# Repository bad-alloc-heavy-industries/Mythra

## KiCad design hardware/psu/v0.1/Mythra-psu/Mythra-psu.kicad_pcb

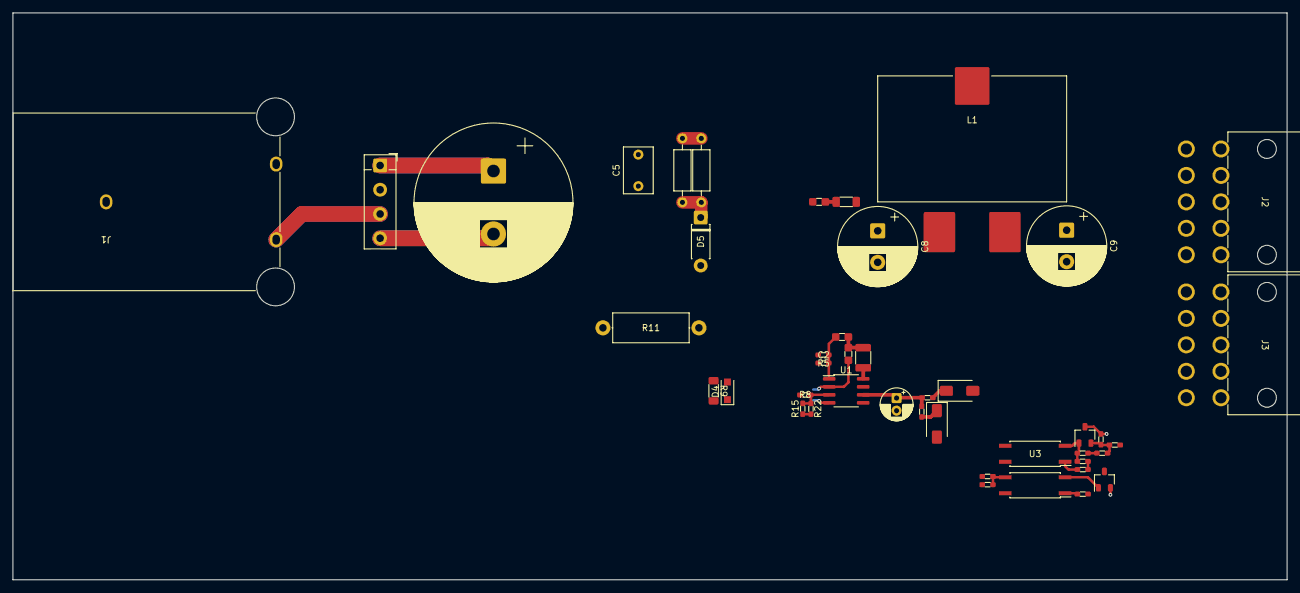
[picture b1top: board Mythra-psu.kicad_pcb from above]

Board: 4 copper layers, 202.3 x 90.0 mm, 45 parts (1 on the bottom side), 30 nets.

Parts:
C1: 470uF @ 450V; CP_Radial_D25.0mm_P10.00mm_SnapIn
C2: 100n; C0603
C3: 22u; CP_Radial_D5.0mm_P2.00mm
C5: 10n; C_Rect_L7.2mm_W4.5mm_P5.00mm_FKS2_FKP2_MKS2_MKP2
C6: 10n; C0603
C7: 1n; C1206
C8, C9: 1m; CP_Radial_D12.5mm_P5.00mm
C10: 1n; C0603
D1: KBP406GTB; Diode_Bridge_Vishay_KBPM
D2: US1M-E3/5AT; D_SMA
D3: 1SMA4744; D_SMA
D4: RB162MM-40; D_SOD-123F
D5: UF4007; D_DO-41_SOD81_P7.62mm_Horizontal
D6: MMBZ5253BLT1G; SOT-23
J1: IEC 320-C14; Schuter-5120.5073.0
J2: Output A; 39-30-1101
J3: Output B; 39-30-1101
L1: 10u; SER2915H
R1, R4: 10M; R0805
R2: 56k; R0603
R3: 0R; R0603
R5: 180k; R0603
R6, R8: 1k; R0603
R7: 50k; R1210
R9: 150R; R1206
R10, R21: 113k; R_Axial_DIN0207_L6.3mm_D2.5mm_P10.16mm_Horizontal
R11: 0R5; R_Axial_DIN0414_L11.9mm_D4.5mm_P15.24mm_Horizontal
R12, R13: 10k; R0603
R14: 10R; R0805
R15, R22: 12k; R0603
R16: 1k5; R0603
R17: 1k2; R0603
R18: 20k; R0603
R19: 60k4; R0603
R20: 6k98; R0603
U1: FAN7602C; SO-8_3.9x4.9mm_P1.27mm
U2, U3: VO617A-8X017T; SO-4_7.6x3.6mm_P2.54mm
U4: AS431BNTR-G1; SOT-23

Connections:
0V: J2.1, J2.2, J2.3, J2.4, J2.5, J3.1, J3.2, J3.3, J3.4, J3.5
+12V: J2.10, J3.10
+24V: J2.6, J2.7, J2.8, J2.9, J3.6, J3.7, J3.8, J3.9
/24V supply/24V: C9.1, L1.2, R13.1, R19.1
/24V supply/FB: R8.2, R15.2, R22.2, U1.3 (CS/FB)
/24V supply/GND: C8.2, C9.2, D6.2 (A), R20.2, U4.3 (A)
/24V supply/LUVP: C2.1, R4.2, R5.1, U1.1 (LUVP)
/24V supply/OUT: D4.1 (K), R9.2, U1.5 (OUT)
/24V supply/PLIM: R1.2, R2.1, R12.1, U1.2 (LAT/PLIM)
/24V supply/VCC: C3.1, R3.1, R6.1, U1.6 (VCC), U2.4, U3.4
/24V supply/VSTR: R7.2, U1.8 (VSTR)
/PRIM+: C1.1, C5.2, D1.1 (+), R1.1, R4.1, R7.1, R10.1, R21.1
/PRIM-: C1.2, C2.2, C3.2, C6.2, D1.4 (-), D3.2 (A), R2.2, R5.2, R11.2, U1.4 (GND)
LINE: D1.2, J1.L
NEUT: D1.3, J1.N
unnamed: C5.1, D5.1 (K), R10.2, R21.2
unnamed: C6.1, R12.2, U2.3
unnamed: C7.1, C8.1, L1.1, R16.1, R17.1
unnamed: C7.2, R14.1
unnamed: C10.1, R19.2, R20.1, U4.2 (REF)
unnamed: C10.2, R18.1
unnamed: D2.1 (K), R3.2
unnamed: D3.1 (K), R6.2
unnamed: D4.2 (A), R9.1
unnamed: D6.1 (K), U2.2
unnamed: R8.1, R11.1
unnamed: R13.2, U2.1
unnamed: R15.1, R22.1, U3.3
unnamed: R16.2, U3.1
unnamed: R17.2, R18.2, U3.2, U4.1 (K)

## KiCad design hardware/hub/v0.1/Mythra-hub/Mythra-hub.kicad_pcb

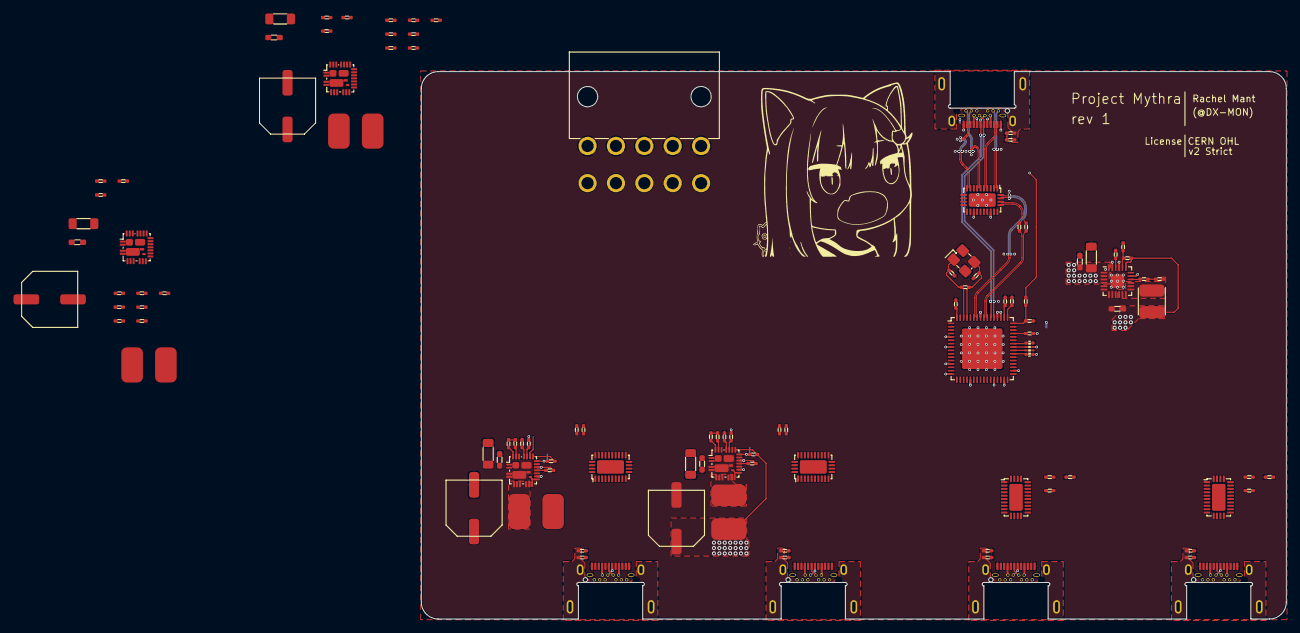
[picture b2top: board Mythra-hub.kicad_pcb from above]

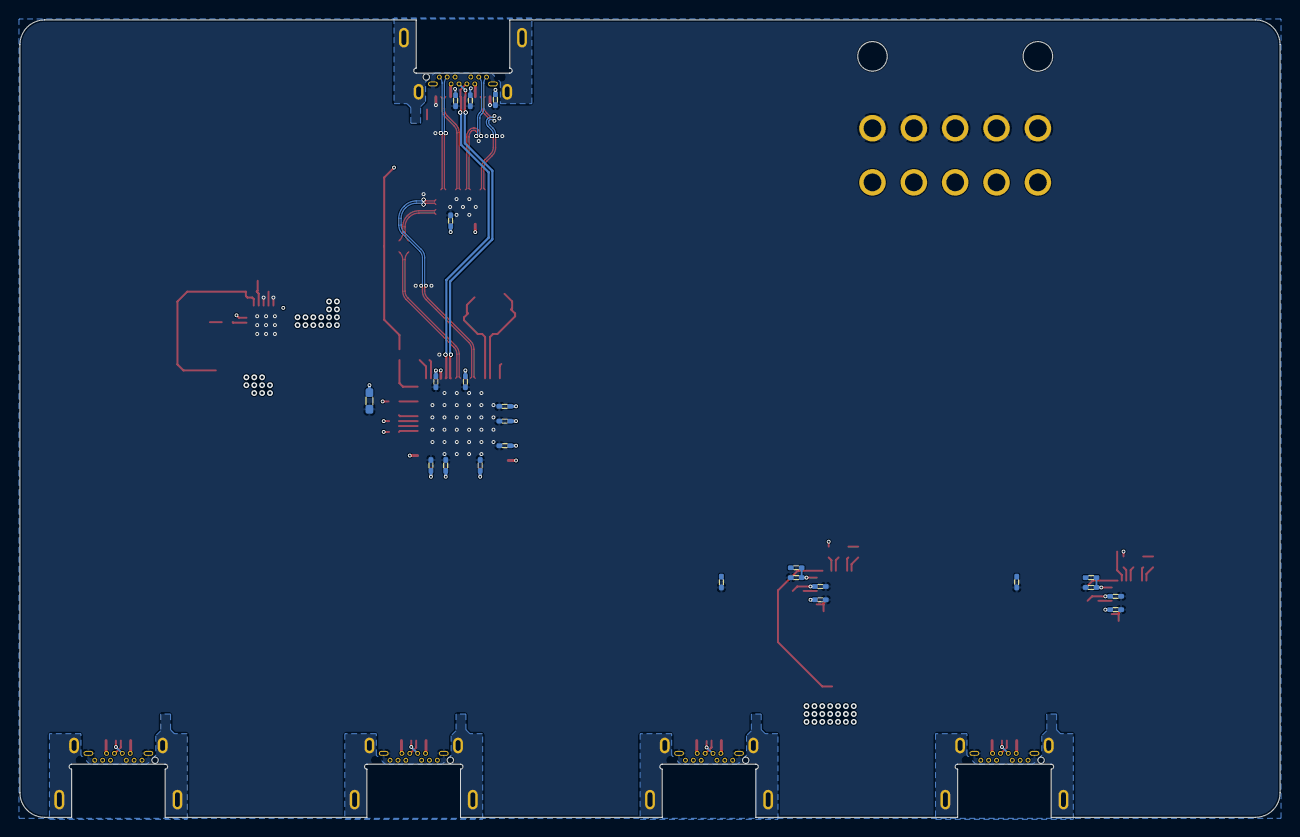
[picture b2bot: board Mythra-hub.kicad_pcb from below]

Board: 6 copper layers, 128.0 x 81.0 mm, 130 parts (23 on the bottom side), 153 nets.

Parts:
C1, C5, C6, C7, C8, C9, C10, C11, C12, C13, C14, C15, C16, C22, C23, C24, C25, C26, C27, C28, C29, C30, C31, C32, C33, C34, C35, C36, C37, C38, C41, C44, C47, C50: 0.1uF; C0402
C2, C3: 15pF; C0402
C4: 260nF; C0402
C17, C18: 10uF; C0603
C19: 22uF; C1206
C20: 22uF; C0603
C21: 4.7uF; C0402
C39, C42, C45, C48: 1uF; C0402
C40, C43, C46, C49: 2.2uF; C0402
C51, C52, C53, C54: 47uF; C_Elec_8.3x8.3mm
C55, C57, C59, C61: 10uF; C1206
C56, C58, C60, C62: 1uF; C0603
J1, J3, J4, J5, J6: 918-418K2022C40000; USB-3.1-Type-C_In-PCB
J2: Molex Power Input; 39-30-1101
L1: 3.3uH; XAL40xx
L2, L3, L4, L5: 6.3µH; SRN6045TA
R1, R4, R14, R15, R16, R17: 1M; R0402
R2: 9k53; R0402
R3, R6, R10, R12, R21, R28, R35, R42: 10k; R0402
R5: 90k9; R0402
R7, R8: 5k1; R0402
R9: 10k; R_Array_Convex_4x0402
R11: 3.4k; R0402
R13: 20R; R0402
R18, R25, R32, R39: 200k; R0402
R19, R26, R33, R40: 51k; R0402
R20, R27, R34, R41: 2R2; R0402
R22, R29, R36, R43: 36.7k; R0402
R23, R30, R37, R44: 14k; R0402
R24, R31, R38, R45: 2.3k; R0402
U1: TUSB8042A; QFN-64-1EP_9x9mm_P0.5mm_EP6x6mm
U2, U4, U5, U6, U7: HD3SS460; WQFN-28-1EP_3.5x5.5_P0.5mm_EP2x4mm
U3: BD95861MUV; VQFN-24-1EP_4x4mm_P0.5mm_EP2x2mm
U8, U9, U10, U11: SiC437/8; MLP44-24L
Y1: 24MHz; SMD3225

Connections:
+1V1: C9.1, C10.1, C11.1, C12.1, C13.1, C14.1, C15.1, C16.1, C17.1, C20.1, L1.2, R11.2, U1.5 (VDD), U1.8 (VDD), U1.13 (VDD), U1.21 (VDD), U1.28 (VDD), U1.31 (VDD), U1.51 (VDD), U1.57 (VDD), U3.19 (VOUT)
+3V3: C8.2, C29.2, C32.2, C35.2, C38.2, R9.4, R9.8, R10.2, U1.16 (VDD33), U1.34 (VDD33), U1.52 (VDD33), U2.17 (EN), U2.22 (VCC), U4.17 (EN), U4.22 (VCC), U5.17 (EN), U5.22 (VCC), U6.17 (EN), U6.22 (VCC), U7.17 (EN), U7.22 (VCC)
+5V: C5.2, J1.A4 (VBUS), J1.A9 (VBUS), J1.B4 (VBUS), J1.B9 (VBUS), R5.1
+12V: C18.1, C19.1, J2.10, U3.1 (VIN), U3.2 (VIN), U3.3 (VIN), U3.4 (VIN), U3.17 (EN), U3.24 (VIN)
+24V: C55.1, C56.1, C57.1, C58.1, C59.1, C60.1, C61.1, C62.1, J2.6, J2.7, J2.8, J2.9, U8.1 (VIN), U8.2 (VIN), U8.22 (VIN), U9.1 (VIN), U9.2 (VIN), U9.22 (VIN), U10.1 (VIN), U10.2 (VIN), U10.22 (VIN), U11.1 (VIN), U11.2 (VIN), U11.22 (VIN)
/DFP1/DFP_D+: J3.A6 (D+), J3.B6 (D+), U1.1 (DN1_D+)
/DFP1/DFP_D-: J3.A7 (D-), J3.B7 (D-), U1.2 (DN1_D-)
/DFP1/DFP_RX1+: J3.B11 (RX1+), U4.1 (CRX1+)
/DFP1/DFP_RX1-: J3.B10 (RX1-), U4.2 (CRX1-)
/DFP1/DFP_RX2+: J3.A11 (RX2+), U4.9 (CRX2+)
/DFP1/DFP_RX2-: J3.A10 (RX2-), U4.10 (CRX2-)
/DFP1/DFP_RX+: U1.6 (DN1_RX+), U4.28 (SSRX+)
/DFP1/DFP_RX-: U1.7 (DN1_RX-), U4.27 (SSRX-)
/DFP1/DFP_SMPS_SW: L2.1, U8.5 (SW), U8.6 (SW), U8.7 (SW), U8.8 (SW), U8.9 (SW)
/DFP1/DFP_SMPS_VDD: C39.1, R19.1, R21.2, U8.15 (VDD)
/DFP1/DFP_TX1+: J3.A2 (TX1+), U4.4 (CTX1+)
/DFP1/DFP_TX1-: J3.A3 (TX1-), U4.5 (CTX1-)
/DFP1/DFP_TX2+: J3.B2 (TX2+), U4.6 (CTX2+)
/DFP1/DFP_TX2-: J3.B3 (TX2-), U4.7 (CTX2-)
/DFP1/DFP_TX+: C27.2, U1.3 (DN1_TX+)
/DFP1/DFP_TX-: C28.2, U1.4 (DN1_TX-)
/DFP1/DFP_TXC+: C27.1, U4.26 (SSTX+)
/DFP1/DFP_TXC-: C28.1, U4.25 (SSTX-)
/DFP1/DFP_VBUS: C51.1, J3.A4 (VBUS), J3.A9 (VBUS), J3.B4 (VBUS), J3.B9 (VBUS), L2.2, R22.1, U8.18 (VOUT)
/DFP1/DN_SHIELD: C23.1, J3.S1 (SHIELD), R14.1
/DFP2/DFP_D+: J4.A6 (D+), J4.B6 (D+), U1.9 (DN2_D+)
/DFP2/DFP_D-: J4.A7 (D-), J4.B7 (D-), U1.10 (DN2_D-)
/DFP2/DFP_RX1+: J4.B11 (RX1+), U5.1 (CRX1+)
/DFP2/DFP_RX1-: J4.B10 (RX1-), U5.2 (CRX1-)
/DFP2/DFP_RX2+: J4.A11 (RX2+), U5.9 (CRX2+)
/DFP2/DFP_RX2-: J4.A10 (RX2-), U5.10 (CRX2-)
/DFP2/DFP_RX+: U1.14 (DN2_RX+), U5.28 (SSRX+)
/DFP2/DFP_RX-: U1.15 (DN2_RX-), U5.27 (SSRX-)
/DFP2/DFP_SMPS_SW: L3.1, U9.5 (SW), U9.6 (SW), U9.7 (SW), U9.8 (SW), U9.9 (SW)
/DFP2/DFP_SMPS_VDD: C42.1, R26.1, R28.2, U9.15 (VDD)
/DFP2/DFP_TX1+: J4.A2 (TX1+), U5.4 (CTX1+)
/DFP2/DFP_TX1-: J4.A3 (TX1-), U5.5 (CTX1-)
/DFP2/DFP_TX2+: J4.B2 (TX2+), U5.6 (CTX2+)
/DFP2/DFP_TX2-: J4.B3 (TX2-), U5.7 (CTX2-)
/DFP2/DFP_TX+: C30.2, U1.11 (DN2_TX+)
/DFP2/DFP_TX-: C31.2, U1.12 (DN2_TX-)
/DFP2/DFP_TXC+: C30.1, U5.26 (SSTX+)
/DFP2/DFP_TXC-: C31.1, U5.25 (SSTX-)
/DFP2/DFP_VBUS: C52.1, J4.A4 (VBUS), J4.A9 (VBUS), J4.B4 (VBUS), J4.B9 (VBUS), L3.2, R29.1, U9.18 (VOUT)
/DFP2/DN_SHIELD: C24.1, J4.S1 (SHIELD), R15.1
/DFP3/DFP_D+: J5.A6 (D+), J5.B6 (D+), U1.17 (DN3_D+)
/DFP3/DFP_D-: J5.A7 (D-), J5.B7 (D-), U1.18 (DN3_D-)
/DFP3/DFP_RX1+: J5.B11 (RX1+), U6.1 (CRX1+)
/DFP3/DFP_RX1-: J5.B10 (RX1-), U6.2 (CRX1-)
/DFP3/DFP_RX2+: J5.A11 (RX2+), U6.9 (CRX2+)
/DFP3/DFP_RX2-: J5.A10 (RX2-), U6.10 (CRX2-)
/DFP3/DFP_RX+: U1.22 (DN3_RX+), U6.28 (SSRX+)
/DFP3/DFP_RX-: U1.23 (DN3_RX-), U6.27 (SSRX-)
/DFP3/DFP_SMPS_SW: L4.1, U10.5 (SW), U10.6 (SW), U10.7 (SW), U10.8 (SW), U10.9 (SW)
/DFP3/DFP_SMPS_VDD: C45.1, R33.1, R35.2, U10.15 (VDD)
/DFP3/DFP_TX1+: J5.A2 (TX1+), U6.4 (CTX1+)
/DFP3/DFP_TX1-: J5.A3 (TX1-), U6.5 (CTX1-)
/DFP3/DFP_TX2+: J5.B2 (TX2+), U6.6 (CTX2+)
/DFP3/DFP_TX2-: J5.B3 (TX2-), U6.7 (CTX2-)
/DFP3/DFP_TX+: C33.2, U1.19 (DN3_TX+)
/DFP3/DFP_TX-: C34.2, U1.20 (DN3_TX-)
/DFP3/DFP_TXC+: C33.1, U6.26 (SSTX+)
/DFP3/DFP_TXC-: C34.1, U6.25 (SSTX-)
/DFP3/DFP_VBUS: C53.1, J5.A4 (VBUS), J5.A9 (VBUS), J5.B4 (VBUS), J5.B9 (VBUS), L4.2, R36.1, U10.18 (VOUT)
/DFP3/DN_SHIELD: C25.1, J5.S1 (SHIELD), R16.1
/DFP4/DFP_D+: J6.A6 (D+), J6.B6 (D+), U1.24 (DN4_D+)
/DFP4/DFP_D-: J6.A7 (D-), J6.B7 (D-), U1.25 (DN4_D-)
/DFP4/DFP_RX1+: J6.B11 (RX1+), U7.1 (CRX1+)
/DFP4/DFP_RX1-: J6.B10 (RX1-), U7.2 (CRX1-)
/DFP4/DFP_RX2+: J6.A11 (RX2+), U7.9 (CRX2+)
/DFP4/DFP_RX2-: J6.A10 (RX2-), U7.10 (CRX2-)
/DFP4/DFP_RX+: U1.29 (DN4_RX+), U7.28 (SSRX+)
/DFP4/DFP_RX-: U1.30 (DN4_RX-), U7.27 (SSRX-)
/DFP4/DFP_SMPS_SW: L5.1, U11.5 (SW), U11.6 (SW), U11.7 (SW), U11.8 (SW), U11.9 (SW)
/DFP4/DFP_SMPS_VDD: C48.1, R40.1, R42.2, U11.15 (VDD)
/DFP4/DFP_TX1+: J6.A2 (TX1+), U7.4 (CTX1+)
/DFP4/DFP_TX1-: J6.A3 (TX1-), U7.5 (CTX1-)
/DFP4/DFP_TX2+: J6.B2 (TX2+), U7.6 (CTX2+)
/DFP4/DFP_TX2-: J6.B3 (TX2-), U7.7 (CTX2-)
/DFP4/DFP_TX+: C36.2, U1.26 (DN4_TX+)
/DFP4/DFP_TX-: C37.2, U1.27 (DN4_TX-)
/DFP4/DFP_TXC+: C36.1, U7.26 (SSTX+)
/DFP4/DFP_TXC-: C37.1, U7.25 (SSTX-)
/DFP4/DFP_VBUS: C54.1, J6.A4 (VBUS), J6.A9 (VBUS), J6.B4 (VBUS), J6.B9 (VBUS), L5.2, R43.1, U11.18 (VOUT)
/DFP4/DN_SHIELD: C26.1, J6.S1 (SHIELD), R17.1
/OC1: R21.1, U1.46 (~OVERCUR1), U8.14 (PGOOD)
/OC2: R28.1, U1.47 (~OVERCUR2), U9.14 (PGOOD)
/OC3: R35.1, U1.44 (~OVERCUR3), U10.14 (PGOOD)
/OC4: R42.1, U1.43 (~OVERCUR4), U11.14 (PGOOD)
/UFP/UFP_RX1+: J1.B11 (RX1+), U2.1 (CRX1+)
/UFP/UFP_RX1-: J1.B10 (RX1-), U2.2 (CRX1-)
/UFP/UFP_RX2+: J1.A11 (RX2+), U2.9 (CRX2+)
/UFP/UFP_RX2-: J1.A10 (RX2-), U2.10 (CRX2-)
/UFP/UFP_RX+: U1.58 (UP_RX+), U2.28 (SSRX+)
/UFP/UFP_RX-: U1.59 (UP_RX-), U2.27 (SSRX-)
/UFP/UFP_TX1+: J1.A2 (TX1+), U2.4 (CTX1+)
/UFP/UFP_TX1-: J1.A3 (TX1-), U2.5 (CTX1-)
/UFP/UFP_TX2+: J1.B2 (TX2+), U2.6 (CTX2+)
/UFP/UFP_TX2-: J1.B3 (TX2-), U2.7 (CTX2-)
/UFP/UFP_TX+: C6.2, U1.55 (UP_TX+)
/UFP/UFP_TX-: C7.2, U1.56 (UP_TX-)
/UFP/UFP_TXC+: C6.1, U2.26 (SSTX+)
/UFP/UFP_TXC-: C7.1, U2.25 (SSTX-)
/UFP/UP_D+: J1.A6 (D+), J1.B6 (D+), U1.53 (UP_D+)
/UFP/UP_D-: J1.A7 (D-), J1.B7 (D-), U1.54 (UP_D-)
/UFP/UP_SHIELD: C1.1, J1.S1 (SHIELD), R1.1
/UFP/UP_VBUS: R5.2, R6.1, U1.48 (USB_VBUS)
GND: C1.2, C2.2, C3.2, C4.2, C5.1, C8.1, C9.2, C10.2, C11.2, C12.2, C13.2, C14.2, C15.2, C16.2, C17.2, C18.2, C19.2, C20.2, C21.2, C23.2, C24.2, C25.2, C26.2, C29.1, C32.1, C35.1, C38.1, C39.2, C40.2, C42.2, C43.2, C45.2, C46.2, C48.2, C49.2, C51.2, C52.2, C53.2, C54.2, C55.2, C56.2, C57.2, C58.2, C59.2, C60.2, C61.2, C62.2, J1.A1 (GND), J1.A12 (GND), J1.B1 (GND), J1.B12 (GND), J2.1, J2.2, J2.3, J2.4, J2.5, J3.A1 (GND), J3.A12 (GND), J3.B1 (GND), J3.B12 (GND), J4.A1 (GND), J4.A12 (GND), J4.B1 (GND), J4.B12 (GND), J5.A1 (GND), J5.A12 (GND), J5.B1 (GND), J5.B12 (GND), J6.A1 (GND), J6.A12 (GND), J6.B1 (GND), J6.B12 (GND), R1.2, R2.2, R3.2, R6.2, R7.2, R8.2, R9.2, R9.6, R12.1, R14.2, R15.2, R16.2, R17.2, R18.1, R24.2, R25.1, R31.2, R32.1, R38.2, R39.1, R45.2, U1.65 (GND), U2.29 (GND), U3.5 (PGND), U3.6 (PGND), U3.7 (PGND), U3.8 (PGND), U3.9 (PGND), U3.21 (GND), U3.23 (TEST), U3.25 (GND), U4.29 (GND), U5.29 (GND), U6.29 (GND), U7.29 (GND), U8.3 (PGND), U8.4 (PGND), U8.13 (PGND), U8.16 (AGND), U8.25 (AGND), U8.27 (PGND), U9.3 (PGND), U9.4 (PGND), U9.13 (PGND), U9.16 (AGND), U9.25 (AGND), U9.27 (PGND), U10.3 (PGND), U10.4 (PGND), U10.13 (PGND), U10.16 (AGND), U10.25 (AGND), U10.27 (PGND), U11.3 (PGND), U11.4 (PGND), U11.13 (PGND), U11.16 (AGND), U11.25 (AGND), U11.27 (PGND), Y1.2, Y1.4
unnamed: C2.1, R4.1, U1.62 (XI), Y1.1
unnamed: C3.1, R4.2, U1.61 (XO), Y1.3
unnamed: C4.1, U1.50 (~GRST)
unnamed: C21.1, U3.22 (VREG)
unnamed: C22.1, R13.2
unnamed: C22.2, L1.1, U3.10 (SW), U3.11 (SW), U3.12 (SW), U3.13 (SW), U3.14 (SW), U3.15 (SW)
unnamed: C40.1, U8.12 (VDRV)
unnamed: C41.1, R20.2
unnamed: C41.2, U8.23 (BOOT)
unnamed: C43.1, U9.12 (VDRV)
unnamed: C44.1, R27.2
unnamed: C44.2, U9.23 (BOOT)
unnamed: C46.1, U10.12 (VDRV)
unnamed: C47.1, R34.2
unnamed: C47.2, U10.23 (BOOT)
unnamed: C49.1, U11.12 (VDRV)
unnamed: C50.1, R41.2
unnamed: C50.2, U11.23 (BOOT)
unnamed: J1.A5 (CC1), R7.1
unnamed: J1.B5 (CC2), R8.1
unnamed: R2.1, U1.64 (USB_R1)
unnamed: R3.1, U1.49 (TEST)
unnamed: R9.1, U1.42 (GANGED/SMBA2/HS_UP)
unnamed: R9.3, U1.41 (PWRCTRL_POL)
unnamed: R9.5, U1.40 (~FULLPWRMGMT/~FULLAUTO/SMBA1/SS_UP)
unnamed: R9.7, U1.39 (~SMBUS/SS_SUSPEND)
unnamed: R10.1, U1.45 (~AUTOEN/HS_SUSPEND)
unnamed: R11.1, R12.2, U3.20 (FB)
unnamed: R13.1, U3.16 (BOOT)
unnamed: R18.2, U8.21 (MODE1)
unnamed: R19.2, U8.20 (MODE2)
unnamed: R20.1, U8.24 (PHASE)
unnamed: R22.2, R23.2, R24.1, U8.17 (FB)
unnamed: R25.2, U9.21 (MODE1)
unnamed: R26.2, U9.20 (MODE2)
unnamed: R27.1, U9.24 (PHASE)
unnamed: R29.2, R30.2, R31.1, U9.17 (FB)
unnamed: R32.2, U10.21 (MODE1)
unnamed: R33.2, U10.20 (MODE2)
unnamed: R34.1, U10.24 (PHASE)
unnamed: R36.2, R37.2, R38.1, U10.17 (FB)
unnamed: R39.2, U11.21 (MODE1)
unnamed: R40.2, U11.20 (MODE2)
unnamed: R41.1, U11.24 (PHASE)
unnamed: R43.2, R44.2, R45.1, U11.17 (FB)

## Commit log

2021-08-01 Added a license and code of conduct for the project
2021-08-01 Added the first chunk of hardware, including the UFP connector, cross-point and the first hub controller
2021-08-07 Added a schematic sheet for the downstream-facing port
2021-08-07 Re-jigged the hierachy and performed some cleanup
2021-08-07 Fixed up the stackup for the PCB and cleaned up after the change
2021-08-08 Added an ignore for the backups dir
2021-08-08 Created the DC-DC supply for the hub's core 1.1V rail and added the DFP Type-C recepticals and their shield components
2021-08-08 Placed and routed the new DC-DC power supply and the DFP connectors
2021-08-15 Fixed some ERC errors in the UFP schematic and the naming of the superspeed signals
2021-08-15 Designed the main part of the per-DFP DC-DC
2021-08-15 Fixed some ERC errors in the main schematic and cleaned up
2021-08-15 Begun laying out the new power supplies and the crosspoints for the DFPs
2021-08-21 part information cleanup in the DFP schematic
2021-08-21 Routed out the last of the per-port DC-DCs, placed and partially routed all the crosspoints
2021-08-29 Added power delivery control to the DFPs
2021-08-29 Routed the new components in and completed route-out of the USB superspeed lines and 2.0 lines
2021-08-29 Fixed some ERC errors
2021-08-29 Fixed a few DRC errors and added ignores for the rest which aren't
2021-09-13 Version controlled the changes from the last stream, including the addition of the 3.3V DC-DC, config I2C EEPROM and test points
2021-09-13 Placed and routed in the new components and done some silkscreen work for the design
2021-09-16 Fixed up some lingering issues with the superspeed routing and the per-port power supplies' DC-DC footprint which was a little off on 3 axies
2021-09-26 Completed a first pass on the azonenburg schematic checklist and begun adding the per-port indicator LEDs that had been forgotten
2021-09-26 Fixed a few issues in the KiCad project and local prefs
2021-09-26 Various fixups caused by the schematic changes and PCB checklist items
2021-09-26 More work toward per-port LED state indicators
2021-09-26 Done more layout work for the indicators
2021-09-27 Cleaned up from adding the indicators
2021-09-27 Clenaed up the DRC violations
2021-09-27 Routed out the LEDs and cleaned up a bit
2021-10-04 Finished working through the fab checklists
2021-10-06 Fixed several issues that cropped up when submitting the PCBs to JLCPCB
2021-10-11 Added the final set of PCB changes that were required to make this manufacturable (RIP In2.Cu being only ground)
2022-01-14 Upgraded the schematic files to KiCad 6 format and done some tidy up from the manufacturing crunch
2022-01-14 Upgraded the KiCad project file to KiCad 6.0 format
2022-01-14 Upgraded the board file to KiCad 6 format and done some tidy up from the manufacturing crunch
2022-02-20 Fixed the PD controller footprints so the gnd on pin 22 was hooked up
2022-05-01 Cleanup in the hub PCB files
2022-05-01 Added the design rules definition file for the hub to the repo
2022-05-01 Begun adding the power supply schematics and board files to the repo
2022-05-01 Added the initial PCB layout and routing for the PSU
2022-05-01 Fixed some mishaps with the PD controller metadata fields and sync'd the schematic and PCB for the hub

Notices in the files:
hardware/hub/v0.1/Mythra-hub/Mythra-hub.kicad_pcb:
CERN OHL
